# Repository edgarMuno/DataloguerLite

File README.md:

# DataloguerLite
Dataloguer basico que soporta sensor de temperatura SHTX, sensor de humedad con protocolo RS485 RTU, sensor de humedad con protocolo SDI-12, puerto analogico, puerto para conexion de actuador. El sistema de monitoreo se le puede configurar el intervalo de medicion, el URL de Ubidots, APN, Direccion de sensores, Numero de sensores y el tipo de sensores mediante la memoria SD. El sistema se alimenta con un panel solar y baterias, y trasmite mediante un modulo GPRS los datos a la pltaforma UBIDOTS para la vizulaizacion.

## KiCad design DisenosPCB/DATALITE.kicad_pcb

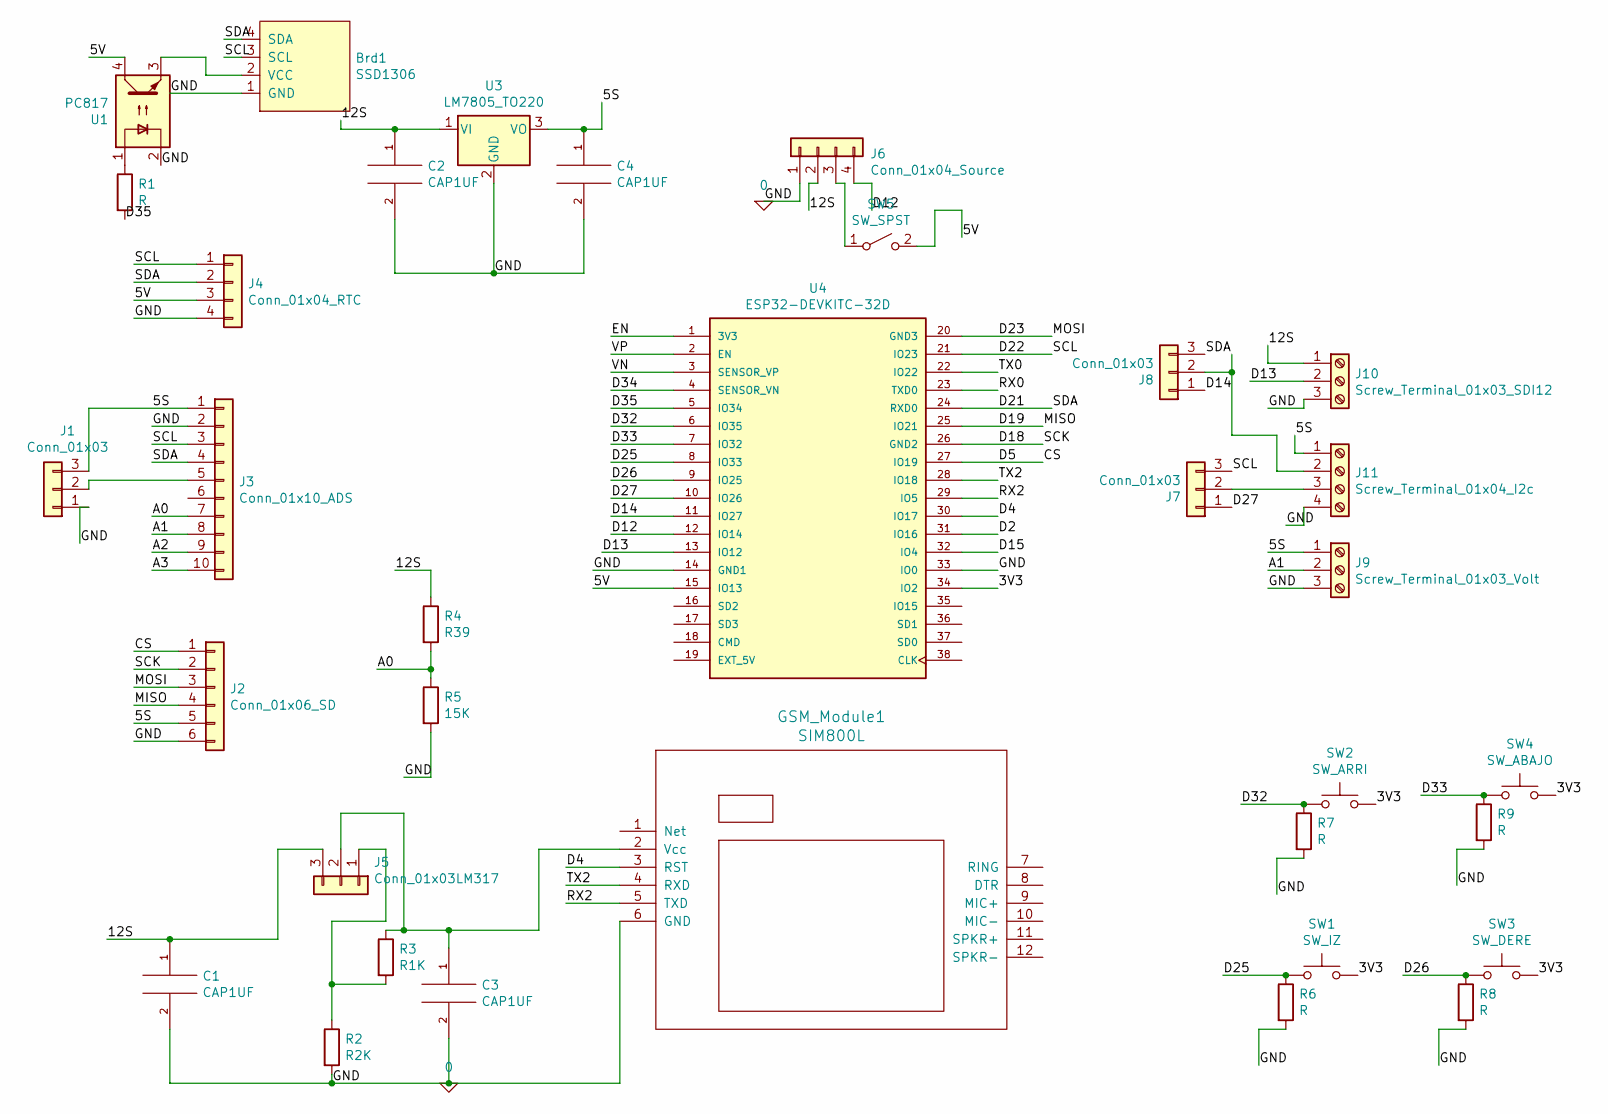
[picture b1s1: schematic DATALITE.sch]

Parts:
Brd1: SSD1306; 128x64OLED
C1, C2, C3, C4: CAP1UF; CP_Radial_D8.0mm_P3.50mm
GSM_Module1: SIM800L
J1, J7, J8: Conn_01x03; PinHeader_1x03_P2.54mm_Vertical
J2: Conn_01x06_SD; PinHeader_1x06_P2.54mm_Vertical
J3: Conn_01x10_ADS; PinHeader_1x10_P2.54mm_Vertical
J4: Conn_01x04_RTC; PinHeader_1x04_P2.54mm_Vertical
J5: Conn_01x03LM317; PinHeader_1x03_P2.54mm_Vertical
J6: Conn_01x04_Source; PinHeader_1x04_P2.54mm_Vertical
J9: Screw_Terminal_01x03_Volt; TerminalBlock_bornier-3_P5.08mm
J10: Screw_Terminal_01x03_SDI12; TerminalBlock_bornier-3_P5.08mm
J11: Screw_Terminal_01x04_I2c; TerminalBlock_bornier-4_P5.08mm
R1, R6, R7, R8, R9: R; R_Axial_DIN0309_L9.0mm_D3.2mm_P12.70mm_Horizontal
R2: R2K; R_Axial_DIN0309_L9.0mm_D3.2mm_P12.70mm_Horizontal
R3: R1K; R_Axial_DIN0309_L9.0mm_D3.2mm_P12.70mm_Horizontal
R4: R39; R_Axial_DIN0309_L9.0mm_D3.2mm_P12.70mm_Horizontal
R5: 15K; R_Axial_DIN0309_L9.0mm_D3.2mm_P12.70mm_Horizontal
SW1: SW_IZ; SW_PUSH_6mm_H4.3mm
SW2: SW_ARRI; SW_PUSH_6mm_H4.3mm
SW3: SW_DERE; SW_PUSH_6mm_H4.3mm
SW4: SW_ABAJO; SW_PUSH_6mm_H4.3mm
SW5: SW_SPST; SW_DIP_SPSTx01_Piano_10.8x4.1mm_W7.62mm_P2.54mm
U1: PC817; DIP-4_W7.62mm
U3: LM7805_TO220; TO-220-3_Vertical
U4: ESP32-DEVKITC-32D; MODULE_ESP32-DEVKITC-32D; PARTREV 4

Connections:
0: Brd1.1 (GND), C1.2, C2.2, C3.2, C4.2, GSM_Module1.6 (GND), J1.1, J2.6, J3.2, J4.4, J6.1, J9.3, J10.3, J11.4, R2.2, R5.2, R6.2, R7.2, R8.2, R9.2, U1.2, U3.2 (GND), U4.14 (GND1), U4.33 (IO0)
/3V3: SW1.2, SW2.2, SW3.2, SW4.2, U4.34 (IO2)
/5S: C4.1, J1.3, J2.5, J3.1, J9.1, J11.1, U3.3 (VO)
/5V: J4.3, SW5.2 (B), U1.4, U4.15 (IO13)
/12S: C1.1, C2.1, J5.3, J6.2, J10.1, R4.1, U3.1 (VI)
/A0: J3.7, R4.2, R5.1
/A1: J3.8, J9.2
/A2: J3.9
/A3: J3.10
/CS: J2.1, U4.27 (IO19)
/D2: U4.31 (IO16)
/D4: GSM_Module1.3 (RST), U4.30 (IO17)
/D12: J6.4, U4.12 (IO14)
/D13: J10.2, U4.13 (IO12)
/D14: J8.1, U4.11 (IO27)
/D15: U4.32 (IO4)
/D18: J2.2, U4.26 (GND2)
/D19: J2.4, U4.25 (IO21)
/D21: Brd1.4 (SDA), J3.4, J4.2, J8.3, U4.24 (RXD0)
/D22: Brd1.3 (SCL), J3.3, J4.1, J7.3, U4.21 (IO23)
/D23: J2.3, U4.20 (GND3)
/D25: R6.1, SW1.1, U4.8 (IO33)
/D26: R8.1, SW3.1, U4.9 (IO25)
/D27: J7.1, U4.10 (IO26)
/D32: R7.1, SW2.1, U4.6 (IO35)
/D33: R9.1, SW4.1, U4.7 (IO32)
/D34: U4.4 (SENSOR_VN)
/D35: R1.2, U4.5 (IO34)
/EN: U4.1 (3V3)
/RX0: U4.23 (TXD0)
/RX2: GSM_Module1.5 (TXD), U4.29 (IO5)
/TX0: U4.22 (IO22)
/TX2: GSM_Module1.4 (RXD), U4.28 (IO18)
/VN: U4.3 (SENSOR_VP)
/VP: U4.2 (EN)
unnamed: Brd1.2 (VCC), U1.3
unnamed: C3.1, GSM_Module1.2 (Vcc), J5.2, R3.1
unnamed: J1.2, J3.5
unnamed: J5.1, R2.1, R3.2
unnamed: J6.3, SW5.1 (A)
unnamed: J8.2, J11.2
unnamed: J7.2, J11.3
unnamed: R1.1, U1.1

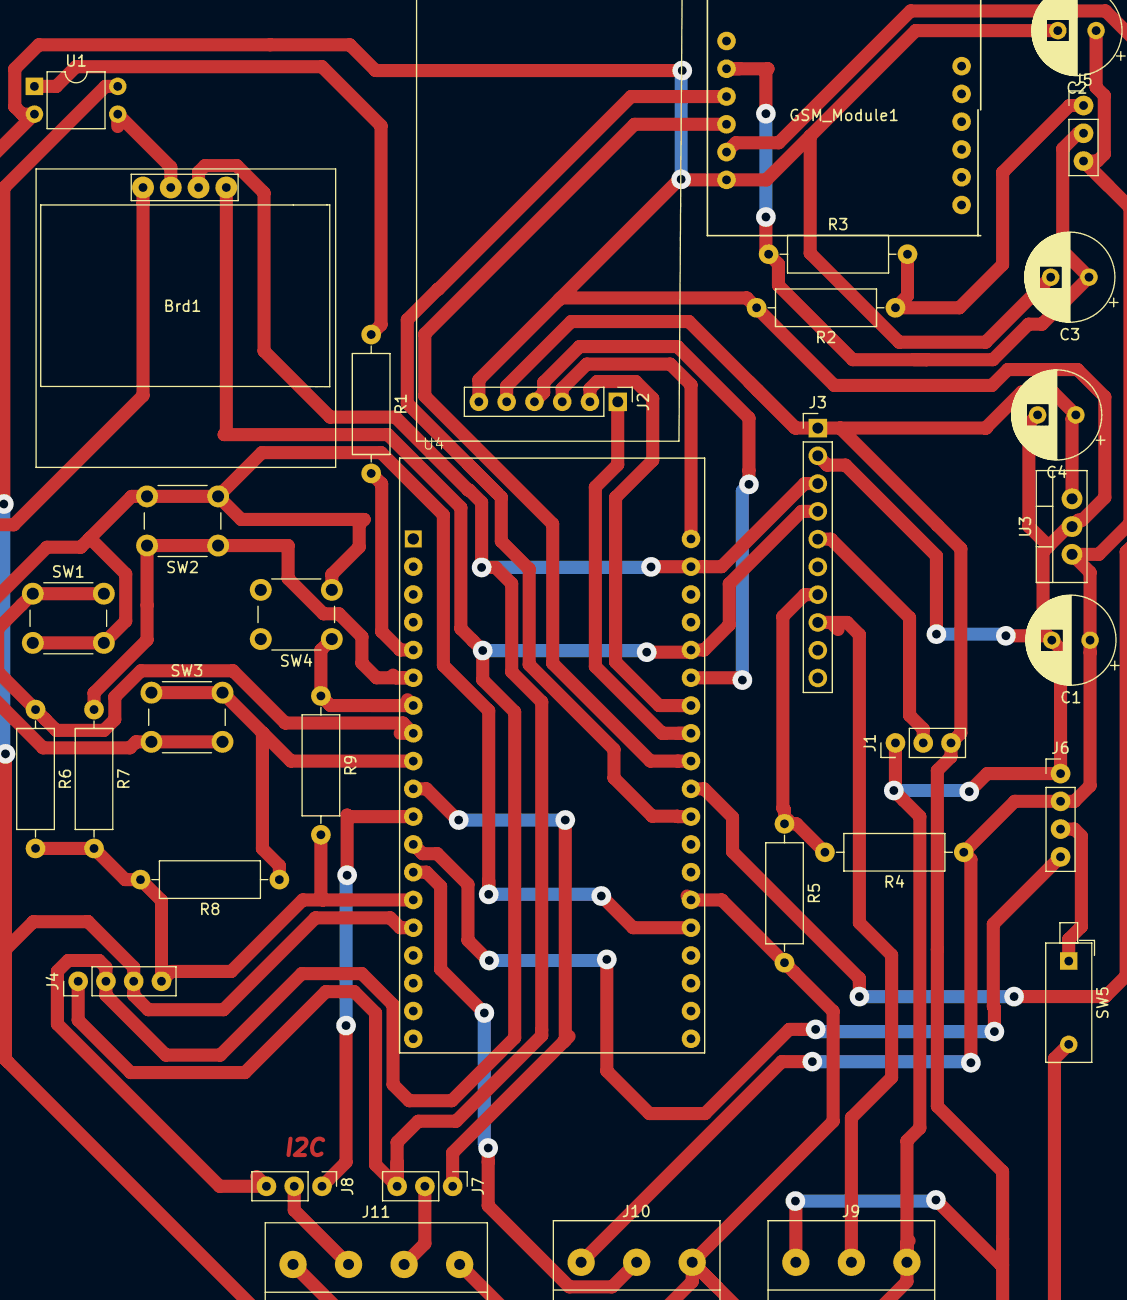
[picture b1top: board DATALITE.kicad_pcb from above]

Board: 2 copper layers, 34 parts (0 on the bottom side), 33 nets.

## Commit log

2022-09-07 Add files via upload
    Funcional, con intervalos de programacion, se realiza la configuracion en la SD.
2022-09-07 Add files via upload
    Los gerbers para realizar el circuito en CNC. Los disenos PCB se realizaron en kiCAD
